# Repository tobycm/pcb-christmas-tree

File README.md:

# PCB Christmas Light

A Christmas tree fixture made out of PCBs and some RGB leds! Powered by CH32V203 MCU, SK6812MINI-E RGB leds, and USB C power input. Equipped with over-current protection, under-voltage protection, and ESD protection. Also includes touch keys and touch sliders for user input.

### Quick View Base Design

### Quick View Leaf Design

## PCB

## BOM

| Description | Quantity | Part # | Unit price | Extended Price USD | Product Link |
| :--- | :---: | :--- | :---: | :---: | :--- |
| Lithium Battery SOT-23-6 Battery Management | 5 | HY2120-CB | 0.251 | 1.26 | https://www.lcsc.com/product-detail/C116509.html |
| Battery Charging IC Battery Balancing IC Lithium-ion/Polymer VQFN-24-EP(4x4) | 2 | IP2326 | 0.6377 | 1.28 | https://www.lcsc.com/product-detail/C2832094.html |
| N-Channel Array 20V 6A 1.5W Surface Mount SOT-23-6L | 10 | FS8205A | 0.058 | 0.58 | https://www.lcsc.com/product-detail/C908265.html |
| 125mW 330Ω 150V Thick Film Resistor ±100ppm/°C ±1% 0805 Chip Resistor - Surface Mount RoHS | 100 | RC0805FR-07330RL | 0.0061 | 0.61 | https://www.lcsc.com/product-detail/C105878.html |
| 22uF ±20% 25V Ceramic Capacitor X5R 0805 | 30 | CL21A226MAYNNNE | 0.1078 | 3.23 | https://www.lcsc.com/product-detail/C602037.html |
| 10uF ±20% 10V Ceramic Capacitor X5R 0603 | 20 | CL10A106MP8NNNC | 0.0173 | 0.35 | https://www.lcsc.com/product-detail/C85713.html |
| Step-down type 600kHz Adjustable 2.5A SOT-23-6 Voltage Regulators - DC DC Switching Regulators | 5 | TP6327GS6-A | 0.3619 | 1.81 | https://www.lcsc.com/product-detail/C2901328.html |
| SMD-4P, 5.4x5mm LED Addressable, Specialty RoHS | 50 | SK6812 | 0.0726 | 3.63 | https://www.lcsc.com/product-detail/C5378720.html |
| 125mW 2kΩ 150V Thin Film Resistor ±50ppm/°C ±0.1% 0805 Chip Resistor - Surface Mount RoHS | 10 | RT0805BRE072KL | 0.0443 | 0.44 | https://www.lcsc.com/product-detail/C706274.html |
| 9.5A 2.2uH ±20% 15mΩ 10A Molded inductor SMD, 7x6.6mm Fixed Inductors RoHS | 10 | APH0630T2R2M | 0.0817 | 0.82 | https://www.lcsc.com/product-detail/C5349701.html |
| RES 180kΩ ±1% 250mW 1206 | 50 | 1206W4F1803T5E | 0.0145 | 0.725 | https://www.lcsc.com/product-detail/C17923.html |
| 5.1kΩ ±1% 100mW 0603 Thick Film Resistor | 100 | FRC0603F5101TS | 0.0015 | 0.15 | https://www.lcsc.com/product-detail/C2907044.html |
| USB-C (USB TYPE-C) Receptacle Connector 16 Position Surface Mount, Right Angle | 20 | TYPE-C 16PIN 2MD(073) | 0.0718 | 1.44 | https://www.lcsc.com/product-detail/C2765186.html |
| 100nF ±10% 50V Ceramic Capacitor X7R 0603 | 100 | CL10B104KB8NNNC | 0.0072 | 0.72 | https://www.lcsc.com/product-detail/C1591.html |
| 56kΩ ±1% 100mW 0603 Thick Film Resistor | 100 | FRC0603F5602TS | 0.0018 | 0.18 | https://www.lcsc.com/product-detail/C2907053.html |
| 100mW 10kΩ 75V Thick Film Resistor ±100ppm/°C ±1% 0603 Chip Resistor - Surface Mount RoHS | 100 | RC0603FR-0710KL | 0.0027 | 0.27 | https://www.lcsc.com/product-detail/C98220.html |
| NTC Thermistor 100kΩ Surface Mount 0603 | 50 | CMFA104J3950HANT | 0.0165 | 0.83 | https://www.lcsc.com/product-detail/C338607.html |
| 82kΩ ±1% 100mW 0603 Thick Film Resistor | 100 | FRC0603F8202TS | 0.0016 | 0.16 | https://www.lcsc.com/product-detail/C2907072.html |
| Purple LED Indication - Discrete 0603 | 50 | XL-1608UVC-04 | 0.0122 | 0.61 | https://www.lcsc.com/product-detail/C7371898.html |
| RISC-V 32 Bit 100MHz QFN-20-EP(3x3) Microcontrollers | 10 | CH572D | 0.312 | 3.12 | https://www.lcsc.com/product-detail/C46597863.html |
| 8pF 50V Ceramic Capacitor NP0 0603 | 100 | CC0603CRNPO9BN8R0 | 0.0066 | 0.66 | https://www.lcsc.com/product-detail/C327316.html |
| Slide Switch SPDT 2A @ 125V Through Hole, Right Angle Rectangular Columnar 12.7mm | 5 | SS12D10G6-WJ | 0.2314 | 1.16 | https://www.lcsc.com/product-detail/C7431059.html |
| 100mW 0Ω 75V Thick Film Resistor ±400ppm/°C ±1% 0603 Chip Resistor - Surface Mount | 100 | FRC0603F0000TS | 0.0015 | 0.15 | https://www.lcsc.com/product-detail/C2906974.html |
| Connector Header 2 position 2mm Pitch 2A Right Angle -25°C~+85°C | 20 | S2B-PH-K-S(LF)(SN) | 0.04 | 0.80 | https://www.lcsc.com/product-detail/C173752.html |
| 74mΩ 2 SOT-583 OR Controllers, Ideal Diodes RoHS | 1 | LM66200DRLR | 0.4213 | 0.4213 | https://www.lcsc.com/product-detail/C3235556.html |
| 4.7uF ±10% 10V Ceramic Capacitor X5R 0603 | 50 | CL10A475KP8NNNC | 0.0128 | 0.64 | https://www.lcsc.com/product-detail/C1705.html |
| 4 480Mbps USB 2.0 QFN-16(3x3) Interface Controllers RoHS | 1 | CH334P | 0.4073 | 0.4073 | https://www.lcsc.com/product-detail/C5373042.html |
| 300kΩ ±1% 250mW 1206 Thick Film Resistor | 100 | FRC1206F3003TS | 0.004 | 0.40 | https://www.lcsc.com/product-detail/C2933671.html |
| LCSC Shipping | 1 | LCSC Shipping | 12.38 | 12.38 | https://www.lcsc.com/ |
| PCB | 1 | PCB | 2 | 2.00 | https://jlcpcb.com/ |
| Stencil | 1 | Stencil | 3.1 | 3.10 | https://jlcpcb.com/ |
| JLCPCB Shipping | 1 | JLCPCB Shipping | 10.12 | 10.12 | https://jlcpcb.com/ |
| 103040 LiPo batteries | 2 | 103040 | 3.97 | 7.94 | https://ydlbattery.com/en-ca/products/3-7v-1200mah-103040-lithium-polymer-ion-battery?variant=42093666959513 |
| YDL Shipping | 1 | YDL Shipping | 6.98 | 6.98 | https://ydlbattery.com/en-ca |
| | | **Total:** | | **69.37** | |

## End notes

Made with <3 by @tobycm

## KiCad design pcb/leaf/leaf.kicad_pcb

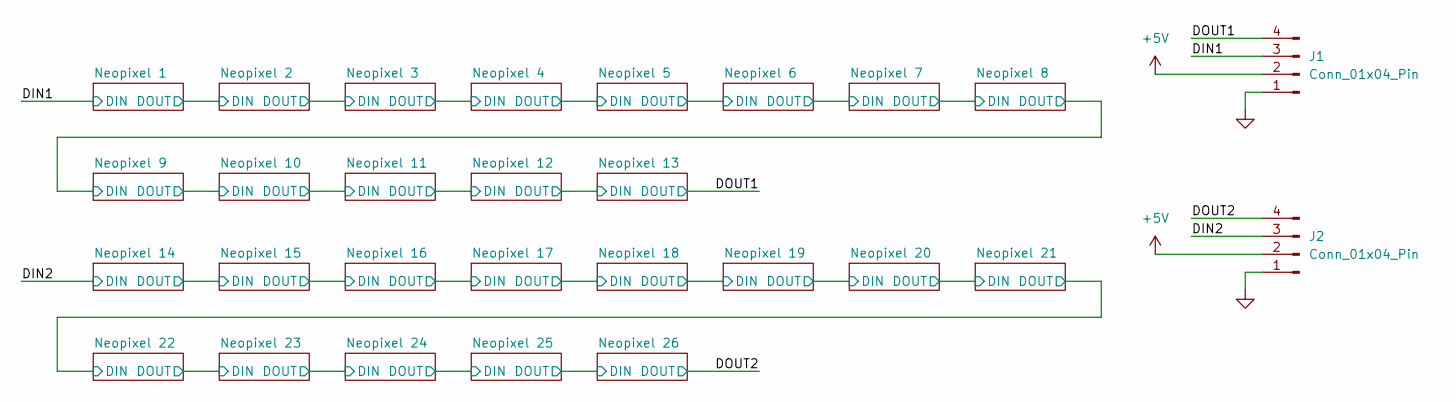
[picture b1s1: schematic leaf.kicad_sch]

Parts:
J1, J2: Conn_01x04_Pin; PinHeader_1x04_P2.54mm_Horizontal

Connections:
+5V: J1.2, J2.2; also elsewhere on the board
/DIN1: J1.3; also elsewhere on the board
/DIN2: J2.3; also elsewhere on the board
/DOUT1: J1.4; also elsewhere on the board
/DOUT2: J2.4; also elsewhere on the board
GND: J1.1, J2.1; also elsewhere on the board

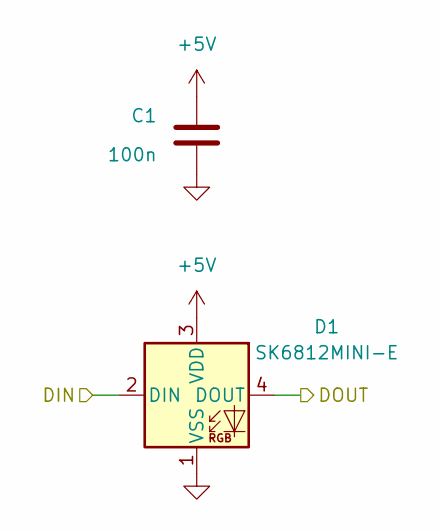
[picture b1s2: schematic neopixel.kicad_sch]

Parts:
C1: 100n; C_0603_1608Metric; LCSC Part C1591
D1: SK6812MINI-E; LED_SK6812MINI-E_3.2x2.8mm_P1.5mm_ReverseMount

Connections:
+5V: C1.1, D1.3 (VDD); also elsewhere on the board
/DIN1: D1.2 (DIN); also elsewhere on the board
/Neopixel 1/DOUT: D1.4 (DOUT); also elsewhere on the board
GND: C1.2, D1.1 (VSS); also elsewhere on the board

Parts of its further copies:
C2, C3, C4, C5, C6, C7, C8, C9, C10, C11, C12, C13, C14, C15, C16, C17, C18, C19, C20, C21, C22, C23, C24, C25, C26: 100n; C_0603_1608Metric; LCSC Part C1591
D2, D3, D4, D5, D6, D7, D8, D9, D10, D11, D12, D13, D14, D15, D16, D17, D18, D19, D20, D21, D22, D23, D24, D25, D26: SK6812MINI-E; LED_SK6812MINI-E_3.2x2.8mm_P1.5mm_ReverseMount

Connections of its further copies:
+5V: C2.1, C3.1, C4.1, C5.1, C6.1, C7.1, C8.1, C9.1, C10.1, C11.1, C12.1, C13.1, C14.1, C15.1, C16.1, C17.1, C18.1, C19.1, C20.1, C21.1, C22.1, C23.1, C24.1, C25.1, C26.1, D2.3 (VDD), D3.3 (VDD), D4.3 (VDD), D5.3 (VDD), D6.3 (VDD), D7.3 (VDD), D8.3 (VDD), D9.3 (VDD), D10.3 (VDD), D11.3 (VDD), D12.3 (VDD), D13.3 (VDD), D14.3 (VDD), D15.3 (VDD), D16.3 (VDD), D17.3 (VDD), D18.3 (VDD), D19.3 (VDD), D20.3 (VDD), D21.3 (VDD), D22.3 (VDD), D23.3 (VDD), D24.3 (VDD), D25.3 (VDD), D26.3 (VDD); also elsewhere on the board
/DIN2: D14.2 (DIN); also elsewhere on the board
/DOUT1: D13.4 (DOUT); also elsewhere on the board
/DOUT2: D26.4 (DOUT); also elsewhere on the board
/Neopixel 1/DOUT: D2.2 (DIN); also elsewhere on the board
/Neopixel 2/DOUT: D2.4 (DOUT), D3.2 (DIN)
/Neopixel 3/DOUT: D3.4 (DOUT), D4.2 (DIN)
/Neopixel 4/DOUT: D4.4 (DOUT), D5.2 (DIN)
/Neopixel 5/DOUT: D5.4 (DOUT), D6.2 (DIN)
/Neopixel 6/DOUT: D6.4 (DOUT), D7.2 (DIN)
/Neopixel 7/DOUT: D7.4 (DOUT), D8.2 (DIN)
/Neopixel 8/DOUT: D8.4 (DOUT), D9.2 (DIN)
/Neopixel 10/DIN: D9.4 (DOUT), D10.2 (DIN)
/Neopixel 10/DOUT: D10.4 (DOUT), D11.2 (DIN)
/Neopixel 11/DOUT: D11.4 (DOUT), D12.2 (DIN)
/Neopixel 12/DOUT: D12.4 (DOUT), D13.2 (DIN)
/Neopixel 14/DOUT: D14.4 (DOUT), D15.2 (DIN)
/Neopixel 15/DOUT: D15.4 (DOUT), D16.2 (DIN)
/Neopixel 16/DOUT: D16.4 (DOUT), D17.2 (DIN)
/Neopixel 17/DOUT: D17.4 (DOUT), D18.2 (DIN)
/Neopixel 18/DOUT: D18.4 (DOUT), D19.2 (DIN)
/Neopixel 19/DOUT: D19.4 (DOUT), D20.2 (DIN)
/Neopixel 20/DOUT: D20.4 (DOUT), D21.2 (DIN)
/Neopixel 21/DOUT: D21.4 (DOUT), D22.2 (DIN)
/Neopixel 22/DOUT: D22.4 (DOUT), D23.2 (DIN)
/Neopixel 23/DOUT: D23.4 (DOUT), D24.2 (DIN)
/Neopixel 24/DOUT: D24.4 (DOUT), D25.2 (DIN)
/Neopixel 25/DOUT: D25.4 (DOUT), D26.2 (DIN)
GND: C2.2, C3.2, C4.2, C5.2, C6.2, C7.2, C8.2, C9.2, C10.2, C11.2, C12.2, C13.2, C14.2, C15.2, C16.2, C17.2, C18.2, C19.2, C20.2, C21.2, C22.2, C23.2, C24.2, C25.2, C26.2, D2.1 (VSS), D3.1 (VSS), D4.1 (VSS), D5.1 (VSS), D6.1 (VSS), D7.1 (VSS), D8.1 (VSS), D9.1 (VSS), D10.1 (VSS), D11.1 (VSS), D12.1 (VSS), D13.1 (VSS), D14.1 (VSS), D15.1 (VSS), D16.1 (VSS), D17.1 (VSS), D18.1 (VSS), D19.1 (VSS), D20.1 (VSS), D21.1 (VSS), D22.1 (VSS), D23.1 (VSS), D24.1 (VSS), D25.1 (VSS), D26.1 (VSS); also elsewhere on the board

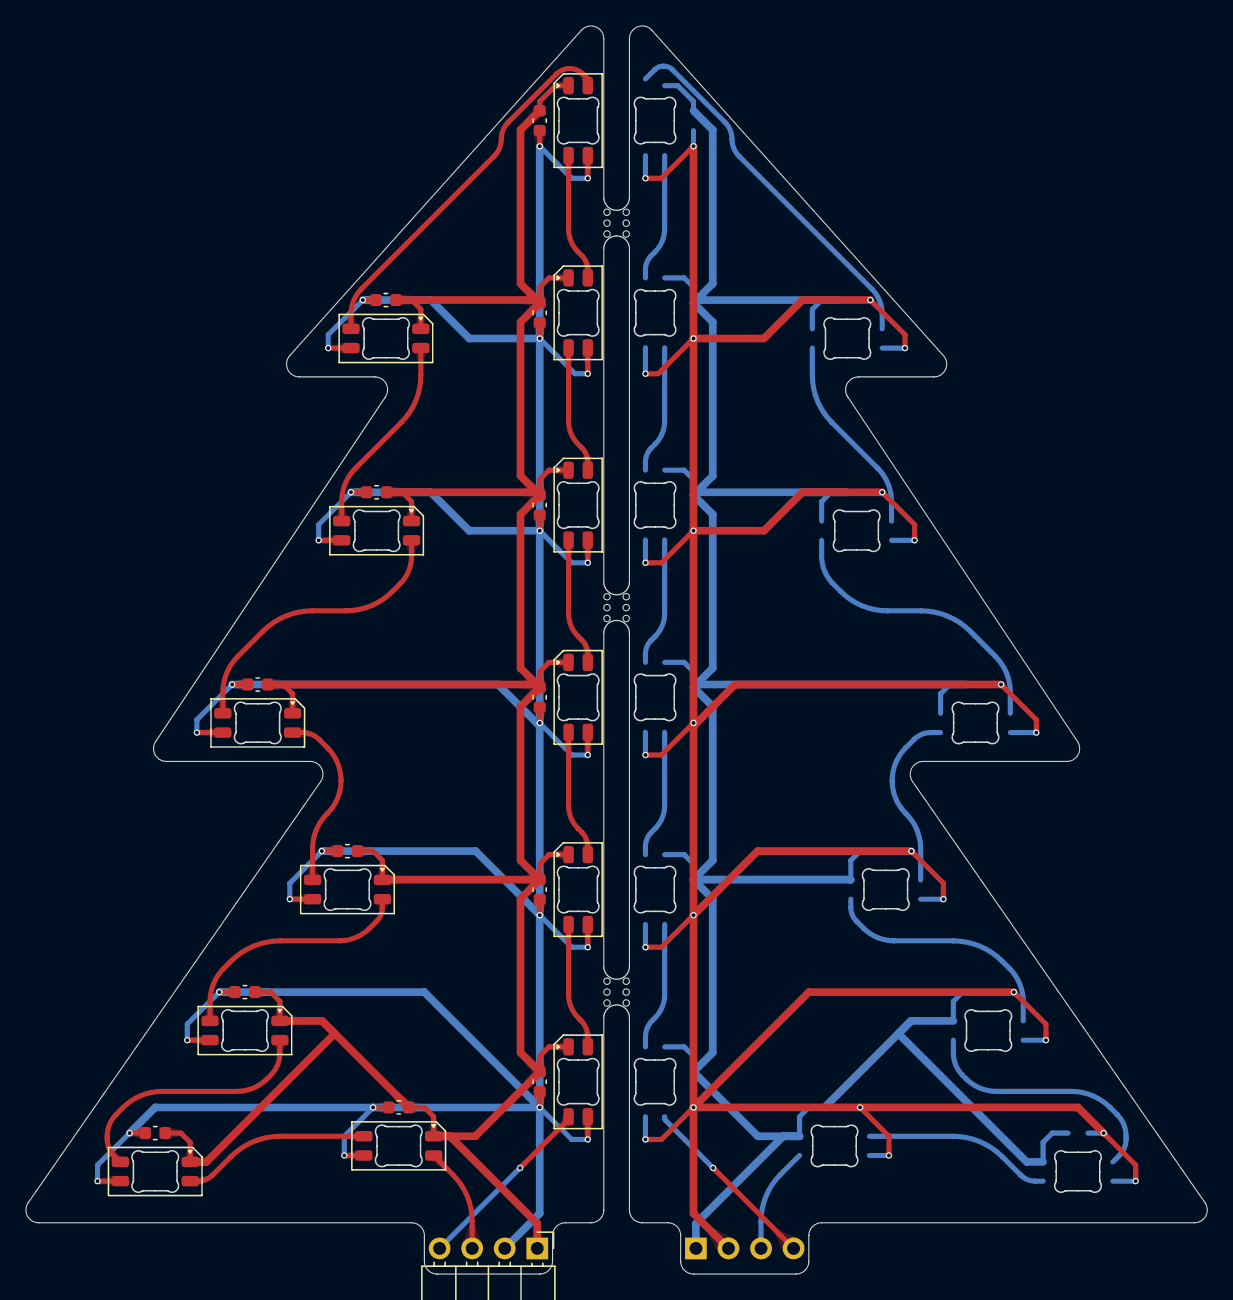
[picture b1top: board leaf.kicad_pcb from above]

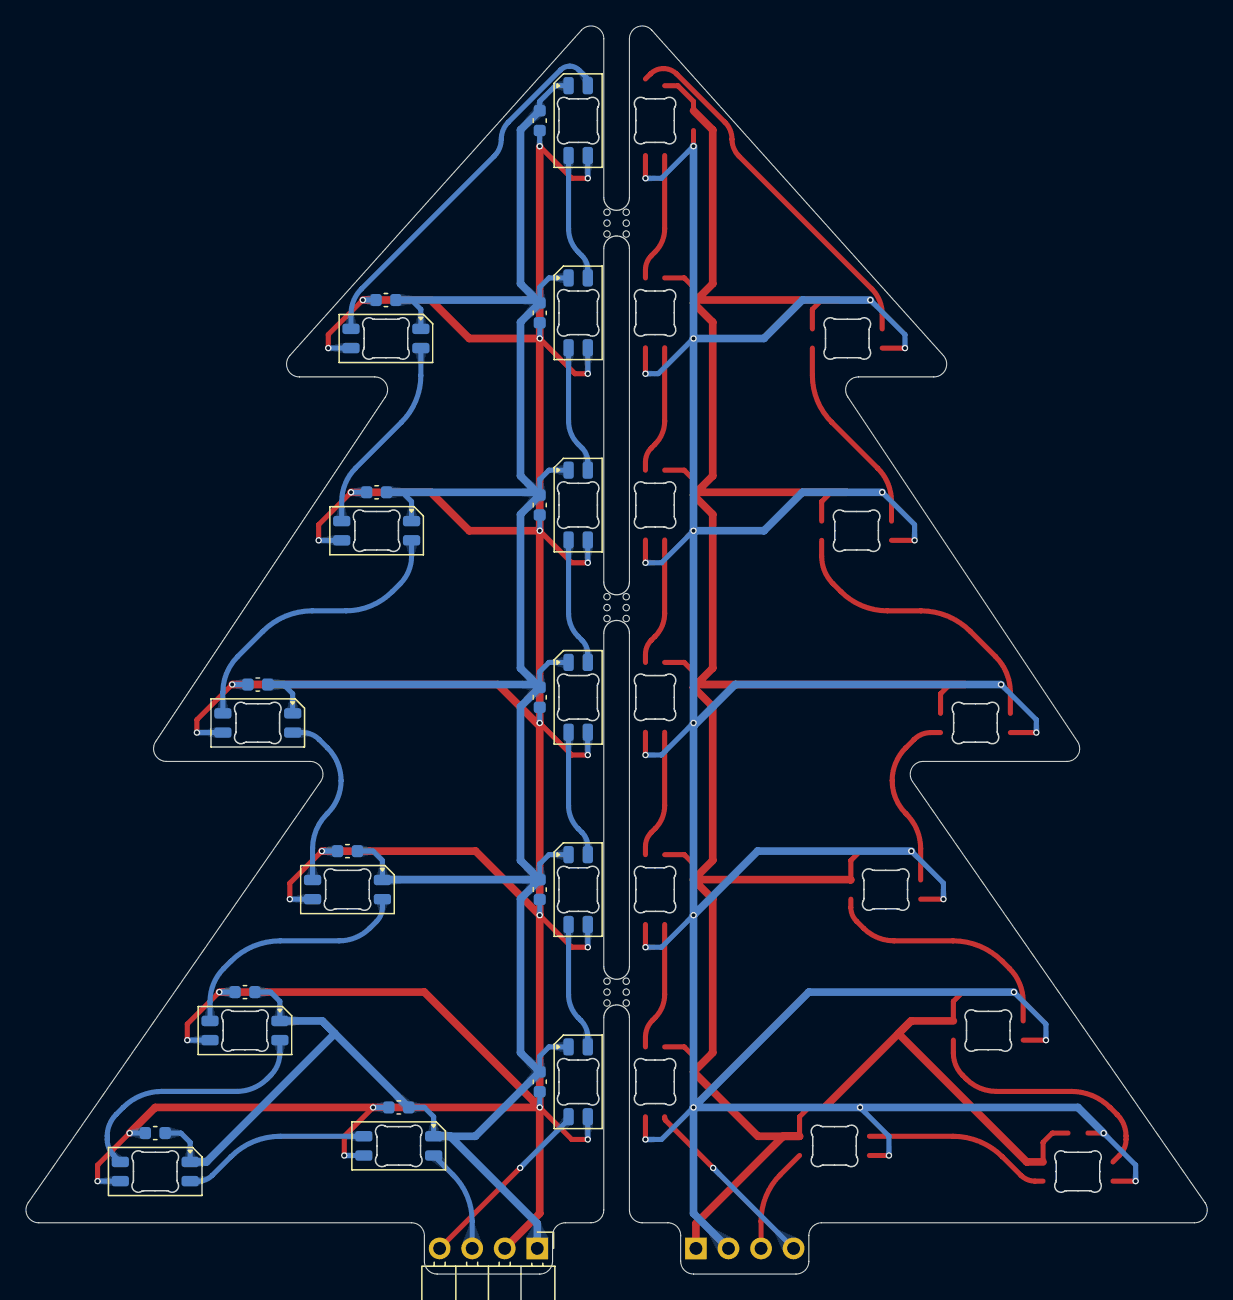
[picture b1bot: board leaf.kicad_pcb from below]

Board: 2 copper layers, 92.2 x 97.4 mm, 54 parts (27 on the bottom side), 30 nets.

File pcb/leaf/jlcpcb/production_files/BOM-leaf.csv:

Comment,Designator,Footprint,LCSC,Quantity
100n,"C1,C10,C11,C12,C13,C14,C15,C16,C17,C18,C19,C2,C20,C21,C22,C23,C24,C25,C26,C3,C4,C5,C6,C7,C8,C9",C_0603_1608Metric,C1591,26
SK6812MINI-E,D2,LED_SK6812MINI-E_3.2x2.8mm_P1.5mm_ReverseMount,,1
SK6812MINI-E,D5,LED_SK6812MINI-E_3.2x2.8mm_P1.5mm_ReverseMount,,1
SK6812MINI-E,D11,LED_SK6812MINI-E_3.2x2.8mm_P1.5mm_ReverseMount,,1
SK6812MINI-E,D12,LED_SK6812MINI-E_3.2x2.8mm_P1.5mm_ReverseMount,,1
SK6812MINI-E,D8,LED_SK6812MINI-E_3.2x2.8mm_P1.5mm_ReverseMount,,1
SK6812MINI-E,D3,LED_SK6812MINI-E_3.2x2.8mm_P1.5mm_ReverseMount,,1
SK6812MINI-E,D9,LED_SK6812MINI-E_3.2x2.8mm_P1.5mm_ReverseMount,,1
SK6812MINI-E,D10,LED_SK6812MINI-E_3.2x2.8mm_P1.5mm_ReverseMount,,1
SK6812MINI-E,D6,LED_SK6812MINI-E_3.2x2.8mm_P1.5mm_ReverseMount,,1
SK6812MINI-E,D4,LED_SK6812MINI-E_3.2x2.8mm_P1.5mm_ReverseMount,,1
Conn_01x04_Pin,J1,PinHeader_1x04_P2.54mm_Horizontal,,1
SK6812MINI-E,D7,LED_SK6812MINI-E_3.2x2.8mm_P1.5mm_ReverseMount,,1
SK6812MINI-E,D1,LED_SK6812MINI-E_3.2x2.8mm_P1.5mm_ReverseMount,,1
SK6812MINI-E,D13,LED_SK6812MINI-E_3.2x2.8mm_P1.5mm_ReverseMount,,1
SK6812MINI-E,D23,LED_SK6812MINI-E_3.2x2.8mm_P1.5mm_ReverseMount,,1
SK6812MINI-E,D19,LED_SK6812MINI-E_3.2x2.8mm_P1.5mm_ReverseMount,,1
SK6812MINI-E,D26,LED_SK6812MINI-E_3.2x2.8mm_P1.5mm_ReverseMount,,1
SK6812MINI-E,D16,LED_SK6812MINI-E_3.2x2.8mm_P1.5mm_ReverseMount,,1
Conn_01x04_Pin,J2,PinHeader_1x04_P2.54mm_Horizontal,,1
SK6812MINI-E,D17,LED_SK6812MINI-E_3.2x2.8mm_P1.5mm_ReverseMount,,1
SK6812MINI-E,D21,LED_SK6812MINI-E_3.2x2.8mm_P1.5mm_ReverseMount,,1
SK6812MINI-E,D14,LED_SK6812MINI-E_3.2x2.8mm_P1.5mm_ReverseMount,,1
SK6812MINI-E,D18,LED_SK6812MINI-E_3.2x2.8mm_P1.5mm_ReverseMount,,1
SK6812MINI-E,D24,LED_SK6812MINI-E_3.2x2.8mm_P1.5mm_ReverseMount,,1
SK6812MINI-E,D22,LED_SK6812MINI-E_3.2x2.8mm_P1.5mm_ReverseMount,,1
SK6812MINI-E,D20,LED_SK6812MINI-E_3.2x2.8mm_P1.5mm_ReverseMount,,1
SK6812MINI-E,D15,LED_SK6812MINI-E_3.2x2.8mm_P1.5mm_ReverseMount,,1
SK6812MINI-E,D25,LED_SK6812MINI-E_3.2x2.8mm_P1.5mm_ReverseMount,,1

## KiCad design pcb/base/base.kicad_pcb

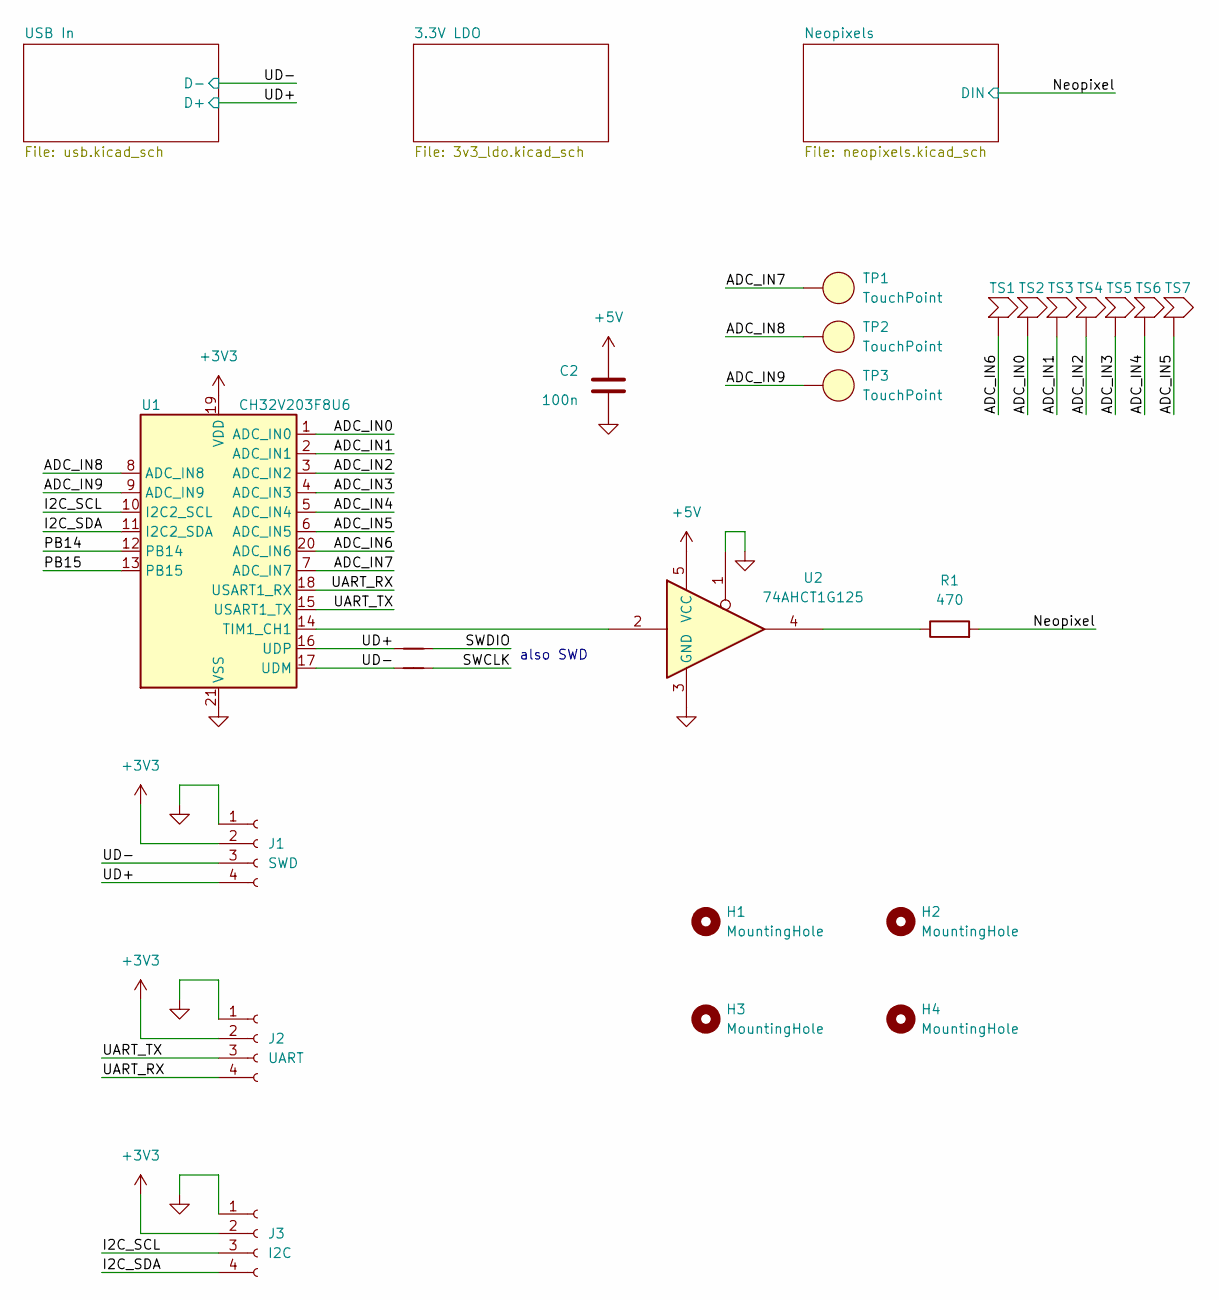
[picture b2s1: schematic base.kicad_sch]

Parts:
C2: 100n; C_0603_1608Metric; LCSC Part C1591
H1, H2, H3, H4: MountingHole; MountingHole_3.2mm_M3_Pad
J1: SWD; PinHeader_1x04_P1.00mm_Vertical
J2: UART; PinHeader_1x04_P1.00mm_Vertical
J3: I2C; PinHeader_1x04_P1.00mm_Vertical
NT1, NT2: NetTie_2
R1: 470; R_0603_1608Metric; LCSC Part C23179
TP1, TP2, TP3: TouchPoint; TouchPoint_Pad_D10.0mm
TS1: TouchSlider; TouchSlider_Start
TS2, TS3, TS4, TS5, TS6: TouchSlider
TS7: TouchSlider; TouchSlider_End
U1: CH32V203F8U6; QFN-20-1EP_3x3mm_P0.4mm_EP1.65x1.65mm; LCSC Part C7570477
U2: 74AHCT1G125; SOT-353_SC-70-5; LCSC Part C52953352

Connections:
+3V3: J1.2, J2.2, J3.2, U1.19 (VDD); also elsewhere on the board
+5V: C2.1, U2.5 (VCC); also elsewhere on the board
/ADC_IN0: TS2.1 (1_1), U1.1 (ADC_IN0)
/ADC_IN1: TS3.1 (1_1), U1.2 (ADC_IN1)
/ADC_IN2: TS4.1 (1_1), U1.3 (ADC_IN2)
/ADC_IN3: TS5.1 (1_1), U1.4 (ADC_IN3)
/ADC_IN4: TS6.1 (1_1), U1.5 (ADC_IN4)
/ADC_IN5: TS7.1 (1_1), U1.6 (ADC_IN5)
/ADC_IN6: TS1.1 (1_1), U1.20 (ADC_IN6)
/ADC_IN7: TP1.1 (1_1), U1.7 (ADC_IN7)
/ADC_IN8: TP2.1 (1_1), U1.8 (ADC_IN8)
/ADC_IN9: TP3.1 (1_1), U1.9 (ADC_IN9)
/I2C_SCL: J3.3, U1.10 (I2C2_SCL)
/I2C_SDA: J3.4, U1.11 (I2C2_SDA)
/Neopixel: R1.2; also elsewhere on the board
/PB14: U1.12 (PB14)
/PB15: U1.13 (PB15)
/UART_RX: J2.4, U1.18 (USART1_RX)
/UART_TX: J2.3, U1.15 (USART1_TX)
/UD+: J1.4, NT1.1, U1.16 (UDP); also elsewhere on the board
/UD-: J1.3, NT2.1, U1.17 (UDM); also elsewhere on the board
GND: C2.2, J1.1, J2.1, J3.1, U1.21 (VSS), U2.1, U2.3 (GND); also elsewhere on the board
unnamed: R1.1, U2.4
unnamed: U1.14 (TIM1_CH1), U2.2

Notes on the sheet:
also SWD

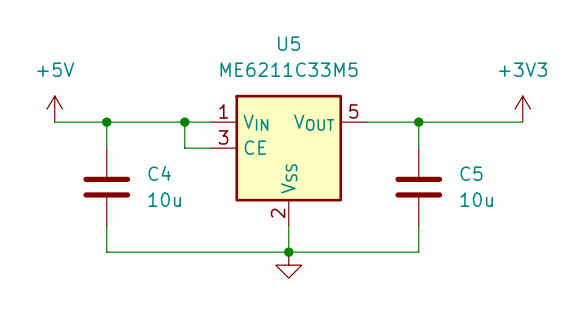
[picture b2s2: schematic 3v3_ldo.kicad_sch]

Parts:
C4, C5: 10u; C_0603_1608Metric; LCSC Part C96446
U5: ME6211C33M5; SOT-23-5; LCSC Part C82942

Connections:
+3V3: C5.2, U5.5 (V_{OUT}); also elsewhere on the board
+5V: C4.2, U5.1 (V_{IN}), U5.3 (CE); also elsewhere on the board
GND: C4.1, C5.1, U5.2 (V_{SS}); also elsewhere on the board

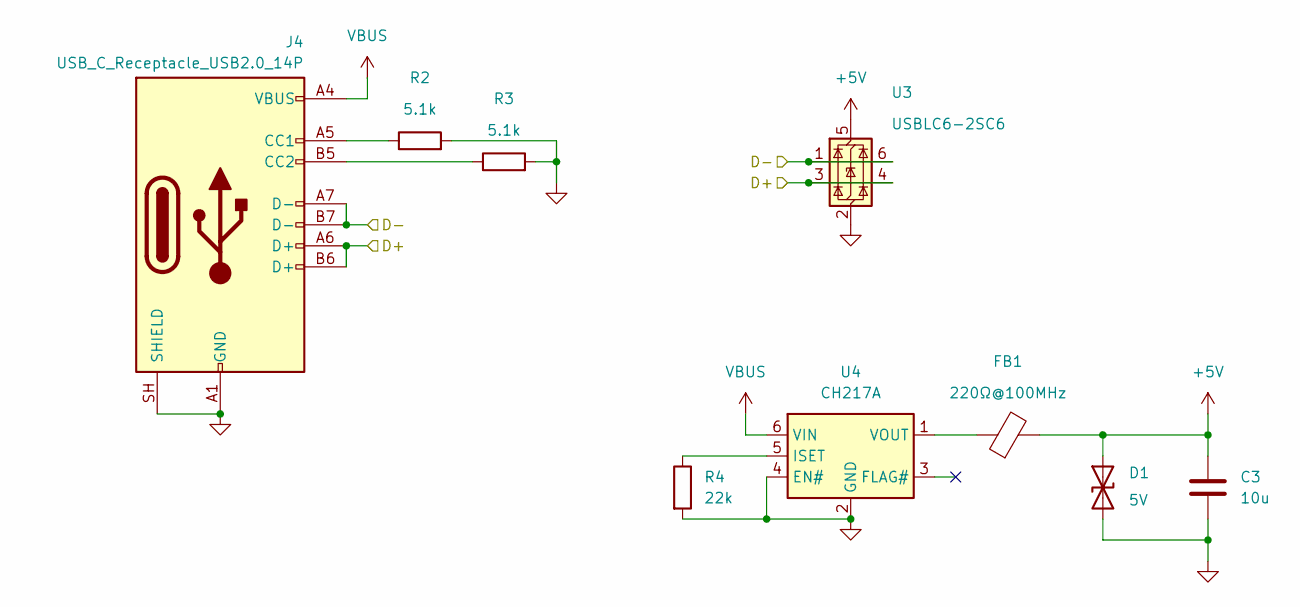
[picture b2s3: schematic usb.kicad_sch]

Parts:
C3: 10u; C_0603_1608Metric; LCSC Part C96446
D1: 5V; D_SOD-523; LCSC Part C82044
FB1: 220Ω@100MHz; R_0805_2012Metric_Pad1.20x1.40mm_HandSolder; LCSC Part C85840
J4: USB_C_Receptacle_USB2.0_14P; USB-C-SMD_TYPE-C-16PIN-2MD-073; LCSC Part C2765186
R2, R3: 5.1k; R_0603_1608Metric; LCSC Part C2907044
R4: 22k; R_0603_1608Metric; LCSC Part C2907015
U3: USBLC6-2SC6; SOT-23-6; LCSC Part C2827654
U4: CH217A; SOT-23-6; LCSC Part C54973763

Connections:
+5V: C3.2, D1.1 (A1), FB1.2, U3.5 (VBUS); also elsewhere on the board
/UD+: J4.A6 (D+), J4.B6 (D+), U3.3 (I/O2), U3.4 (I/O2); also elsewhere on the board
/UD-: J4.A7 (D-), J4.B7 (D-), U3.1 (I/O1), U3.6 (I/O1); also elsewhere on the board
GND: C3.1, D1.2 (A2), J4.A1 (GND), J4.A12 (GND), J4.B1 (GND), J4.B12 (GND), J4.SH (SHIELD), R2.2, R3.2, R4.2, U3.2 (GND), U4.2 (GND), U4.4 (EN#); also elsewhere on the board
unnamed: J4.A5 (CC1), R2.1
unnamed: J4.B5 (CC2), R3.1
unnamed: R4.1, U4.5 (ISET)
unnamed: FB1.1, U4.1 (VOUT)
VBUS: J4.A4 (VBUS), J4.A9 (VBUS), J4.B4 (VBUS), J4.B9 (VBUS), U4.6 (VIN)

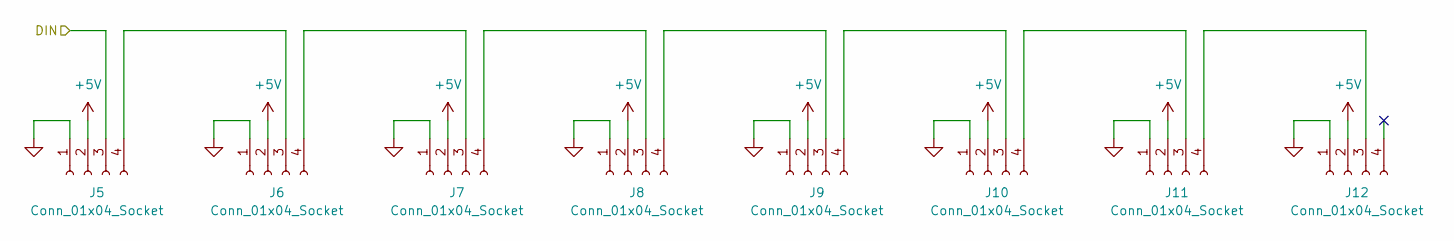
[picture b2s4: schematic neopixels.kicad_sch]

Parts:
J5, J6, J7, J8, J9, J10, J11, J12: Conn_01x04_Socket; PinSocket_1x04_P2.54mm_Vertical

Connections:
+5V: J5.2, J6.2, J7.2, J8.2, J9.2, J10.2, J11.2, J12.2; also elsewhere on the board
/Neopixel: J5.3; also elsewhere on the board
GND: J5.1, J6.1, J7.1, J8.1, J9.1, J10.1, J11.1, J12.1; also elsewhere on the board
unnamed: J5.4, J6.3
unnamed: J6.4, J7.3
unnamed: J7.4, J8.3
unnamed: J8.4, J9.3
unnamed: J9.4, J10.3
unnamed: J10.4, J11.3
unnamed: J11.4, J12.3

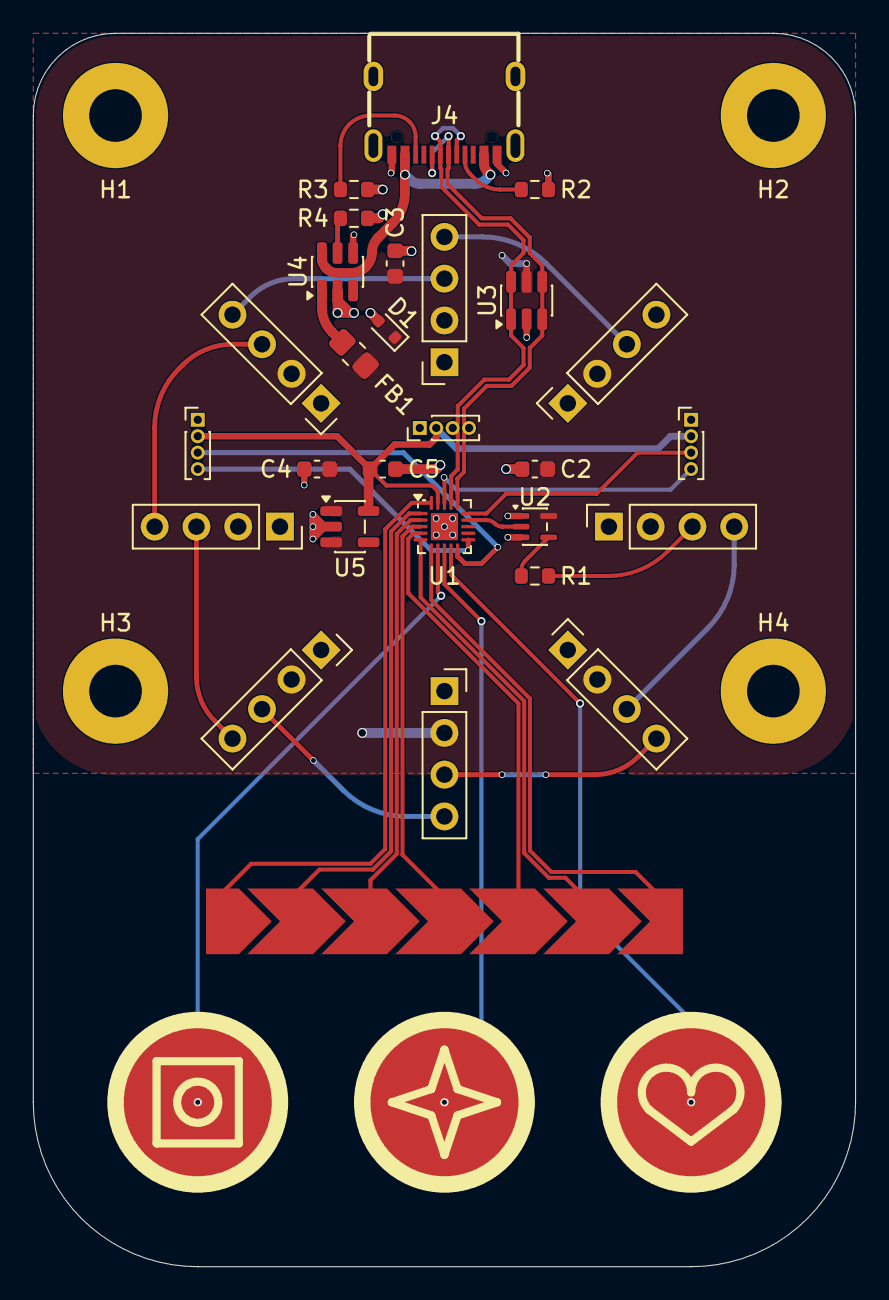
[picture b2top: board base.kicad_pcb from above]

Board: 2 copper layers, 50.0 x 75.0 mm, 41 parts (0 on the bottom side), 34 nets.

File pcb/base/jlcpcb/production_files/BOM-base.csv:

Comment,Designator,Footprint,LCSC,Quantity
100n,C2,C_0603_1608Metric,C1591,1
10u,"C3,C4,C5",C_0603_1608Metric,C96446,3
220Ω@100MHz,FB1,R_0805_2012Metric_Pad1.20x1.40mm_HandSolder,C85840,1
22k,R4,R_0603_1608Metric,C2907015,1
470,R1,R_0603_1608Metric,C23179,1
5.1k,"R2,R3",R_0603_1608Metric,C2907044,2
5V,D1,D_SOD-523,C82044,1
74AHCT1G125,U2,SOT-353_SC-70-5,C52953352,1
CH217A,U4,SOT-23-6,C54973763,1
CH32V203F8U6,U1,QFN-20-1EP_3x3mm_P0.4mm_EP1.65x1.65mm,C7570477,1
ME6211C33M5,U5,SOT-23-5,C82942,1
USBLC6-2SC6,U3,SOT-23-6,C2827654,1
USB_C_Receptacle_USB2.0_14P,J4,USB-C-SMD_TYPE-C-16PIN-2MD-073,C2765186,1
Conn_01x04_Socket,J6,PinSocket_1x04_P2.54mm_Vertical,,1
Conn_01x04_Socket,J10,PinSocket_1x04_P2.54mm_Vertical,,1
Conn_01x04_Socket,J11,PinSocket_1x04_P2.54mm_Vertical,,1
Conn_01x04_Socket,J5,PinSocket_1x04_P2.54mm_Vertical,,1
Conn_01x04_Socket,J9,PinSocket_1x04_P2.54mm_Vertical,,1
Conn_01x04_Socket,J7,PinSocket_1x04_P2.54mm_Vertical,,1
Conn_01x04_Socket,J12,PinSocket_1x04_P2.54mm_Vertical,,1
Conn_01x04_Socket,J8,PinSocket_1x04_P2.54mm_Vertical,,1
UART,J2,PinHeader_1x04_P1.00mm_Vertical,,1
SWD,J1,PinHeader_1x04_P1.00mm_Vertical,,1
I2C,J3,PinHeader_1x04_P1.00mm_Vertical,,1
